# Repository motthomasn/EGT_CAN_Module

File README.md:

# EGT_CAN_Module
Teensy 3.2 based controller board designed to amplify K-Type thermocouple signals and transmit the data digitally via CAN-Bus

This module was built for a turbocharged motorcycle project but has been repurposed for a number of other applications. The aim was to have a flexible method of amplifying signals from K-Type thermocouples and transmitting the data digitally via CAN-Bus to an ECU or datalogger.

The module uses 5off Maxim MAX31855 digital thermocouple converters to process the K-Type signals and a Teensy 3.2 development board to retrieve & broadcast the data. The allowance for 5off K-Type sensors was included specifically for turbocharged 4 cylinder applications (4off port temperatures and 1off turbine inlet temperature), however if fewer sensors are needed then the additional amplifier IC's can just be omitted and the code adjusted to compensate.

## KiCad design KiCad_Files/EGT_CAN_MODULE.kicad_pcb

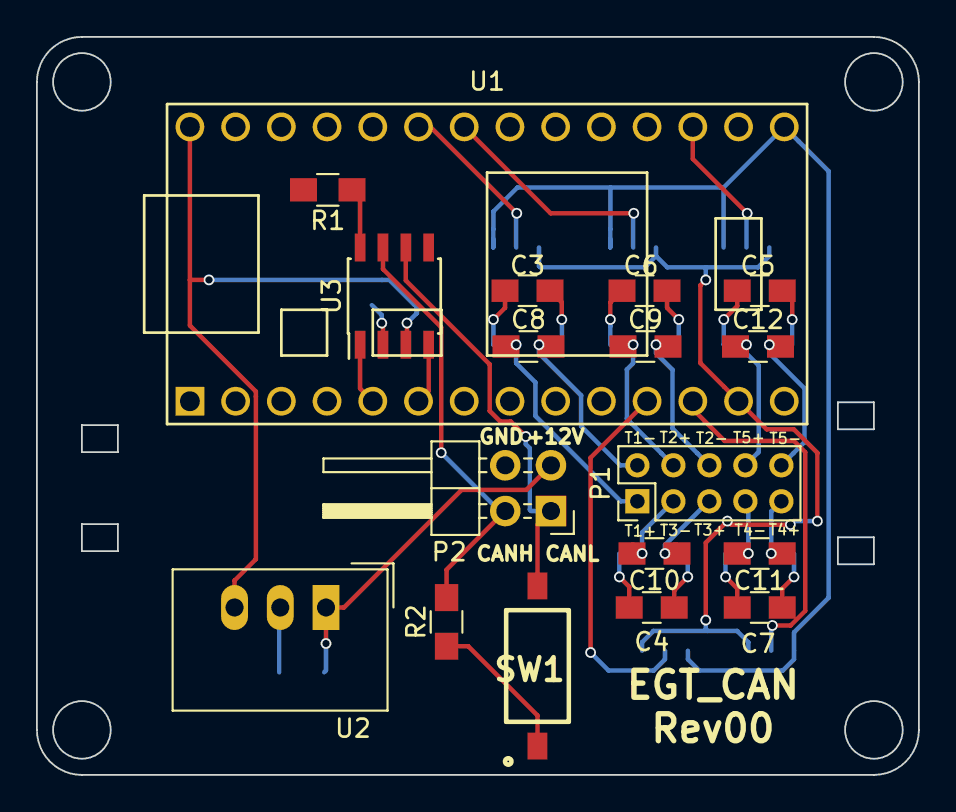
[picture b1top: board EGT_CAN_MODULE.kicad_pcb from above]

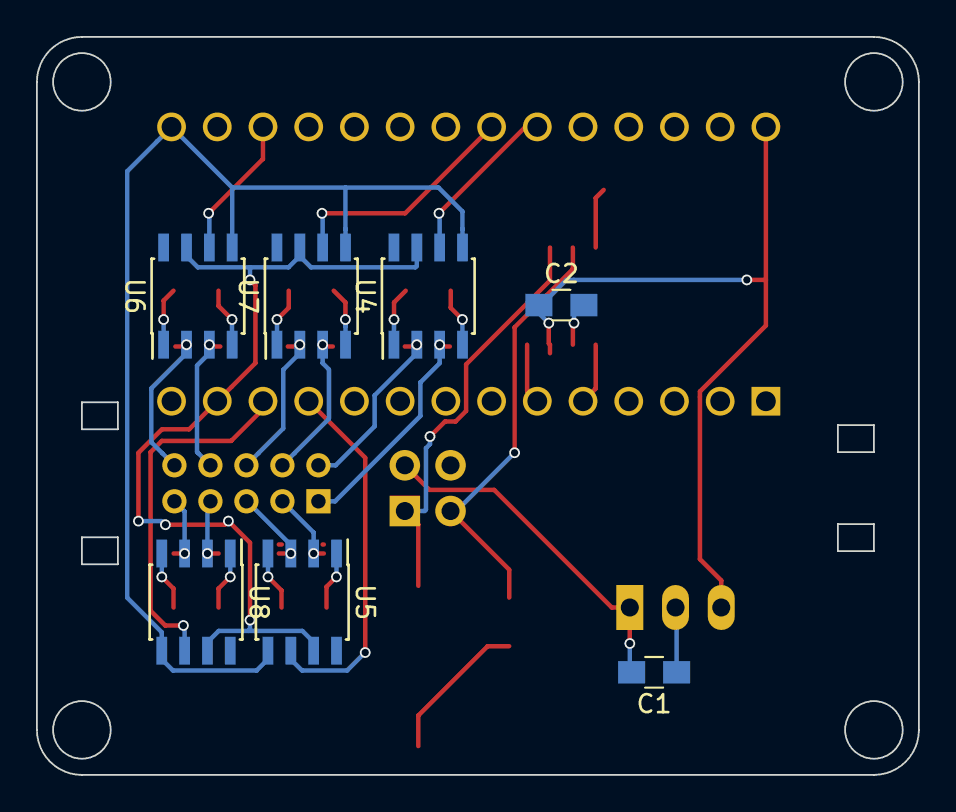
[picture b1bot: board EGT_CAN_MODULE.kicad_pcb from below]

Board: 2 copper layers, 49.0 x 41.0 mm, 25 parts (7 on the bottom side), 27 nets.

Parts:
C1: 22uF; C_0805_HandSoldering
C2, C3, C4, C5, C6, C7: 100nF; C_0805_HandSoldering
C8, C9, C10, C11, C12: 10nF; C_0805_HandSoldering
P1: CONN_01X10; Pin_Header_Straight_2x05_Pitch2.00mm
P2: CONN_01X04; Pin_Header_Angled_2x02_Pitch2.54mm
R1: 18K; R_0805_HandSoldering
R2: 120; R_0805_HandSoldering
SW1: SW_DIP_x01; IKD0103101
U1: TEENSY_3.2_BASIC
U2: TSR_1-2450; DCDC-Conv_TRACO_TSR-1
U3: MCP2551-I/SN; SOIC-8_3.9x4.9mm_Pitch1.27mm
U4, U5, U6, U7, U8: MAX31855KASA; SOIC-8_3.9x4.9mm_Pitch1.27mm

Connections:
+3V3: C3.2, C4.2, C5.2, C6.2, C7.2, U1.26, U4.4, U5.4, U6.4, U7.4, U8.4
+5V: C2.2, U1.28, U2.3, U3.3
+12V: C1.1, P2.1, U2.1
CANH: P2.4, R2.2, U3.7
CANL: P2.3, SW1.2, U3.6
CS_1: U1.23, U4.6
CS_2: U1.22, U7.6
CS_3: U1.11, U5.6
CS_4: U1.12, U8.6
CS_5: U1.17, U6.6
Earth: C1.2, C2.1, C3.1, C4.1, C5.1, C6.1, C7.1, P2.2, R1.2, U1.1, U2.2, U3.2, U4.1, U5.1, U6.1, U7.1, U8.1
unnamed: R1.1, U3.8
unnamed: R2.1, SW1.1
RX_CAN: U1.6, U3.4
SCK_TC: U1.16, U4.5, U5.5, U6.5, U7.5, U8.5
SO_TC: U1.13, U4.7, U5.7, U6.7, U7.7, U8.7
T1+: C8.2, P1.1, U4.3
T1-: C8.1, P1.2, U4.2
T2+: C9.2, P1.4, U7.3
T2-: C9.1, P1.6, U7.2
T3+: C10.2, P1.5, U5.3
T3-: C10.1, P1.3, U5.2
T4+: C11.2, P1.9, U8.3
T4-: C11.1, P1.7, U8.2
T5+: C12.2, P1.8, U6.3
T5-: C12.1, P1.10, U6.2
TX_CAN: U1.5, U3.1

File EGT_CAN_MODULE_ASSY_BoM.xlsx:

Designation | Description | Value | Manufacturer | Part Number | Package | Supplier | Stock No. / Order Code
U1 | Teensy 3.2 |  | PJRC | Teensy 3.2 | PDIP | HobbyTronics
 | Teensy Connector Socket | 14-way, 1 Row, 2.54mm Socket | Harwin | M20-7823646 |  | RS | 488-1724
U2 | Board Power Regulator | 5V, 1A | Traco Power | TSR 1-2450 | SIP 3 | RS | 666-4379
U3 | CAN Transceiver |  | Microchip | MCP2551-I/SN | SOIC 8 | RS | 738-6036
U4,U5,U6,U7,U8 | K-Type Thermocouple Amplifier |  | Maxim Integrated | MAX31855KASA+ | SOIC 8 | RS | 786-1017
C1 | Power Reg Smoothing Cap | 22µF | Murata | GRM219B30G226ME66D | 0805 | RS | 798-4624
C2 | CAN Transciever Input Smoothing Cap | 100nF | AVX | 08055C104KAT2A | 0805 | RS | 464-6688
C3,C4,C5,C6,C7 | Amplifier Input Smoothing Cap | 100nF | AVX | 08055C104KAT2A | 0805 | RS | 464-6688
C8, C9, C10, C11, C12 | K-Type Noise Filter Cap | 10nF | AVX | 08055C103KAT2A | 0805 | RS | 464-6672
R1 | CAN Transciever Reset Resistor | 18K | TE Connectivity | CRG0805F18K | 0805 | RS | 223-0590
R2 | CAN Termination Resistor | 120 | Panasonic | ERJP06F1200V | 0805 | RS | 721-7674
SW1 | CAN Termination Resistor Switch | Single SPST | APEM | IKD0103101 |  | RS | 877-2233
P1 | K-Type Interface Connector
P2 | Board Connector | 4-Way, 2 Row, 2.54mm Right Angle Pin Header | RS PRO | 251-8660 |  | RS | 251-8660

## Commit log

2023-06-13 Update main.cpp to v1.2
    CAN ID adjusted to match CBR250RRi CAN Config v3.0
